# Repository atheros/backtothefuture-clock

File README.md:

Back To The Future Time Circuit Clock
=====================================

About
-----

This repository contains or documents and source code related to my Back To The Future Time Circuit Clock project.

All project details are hosted on hackaday.io: http://hackaday.io/project/709-Back-To-The-Future-Time-Circuit-Clock

This project is part of Hackaday Porjects Sci-Fi contest: http://hackaday.io/page/276

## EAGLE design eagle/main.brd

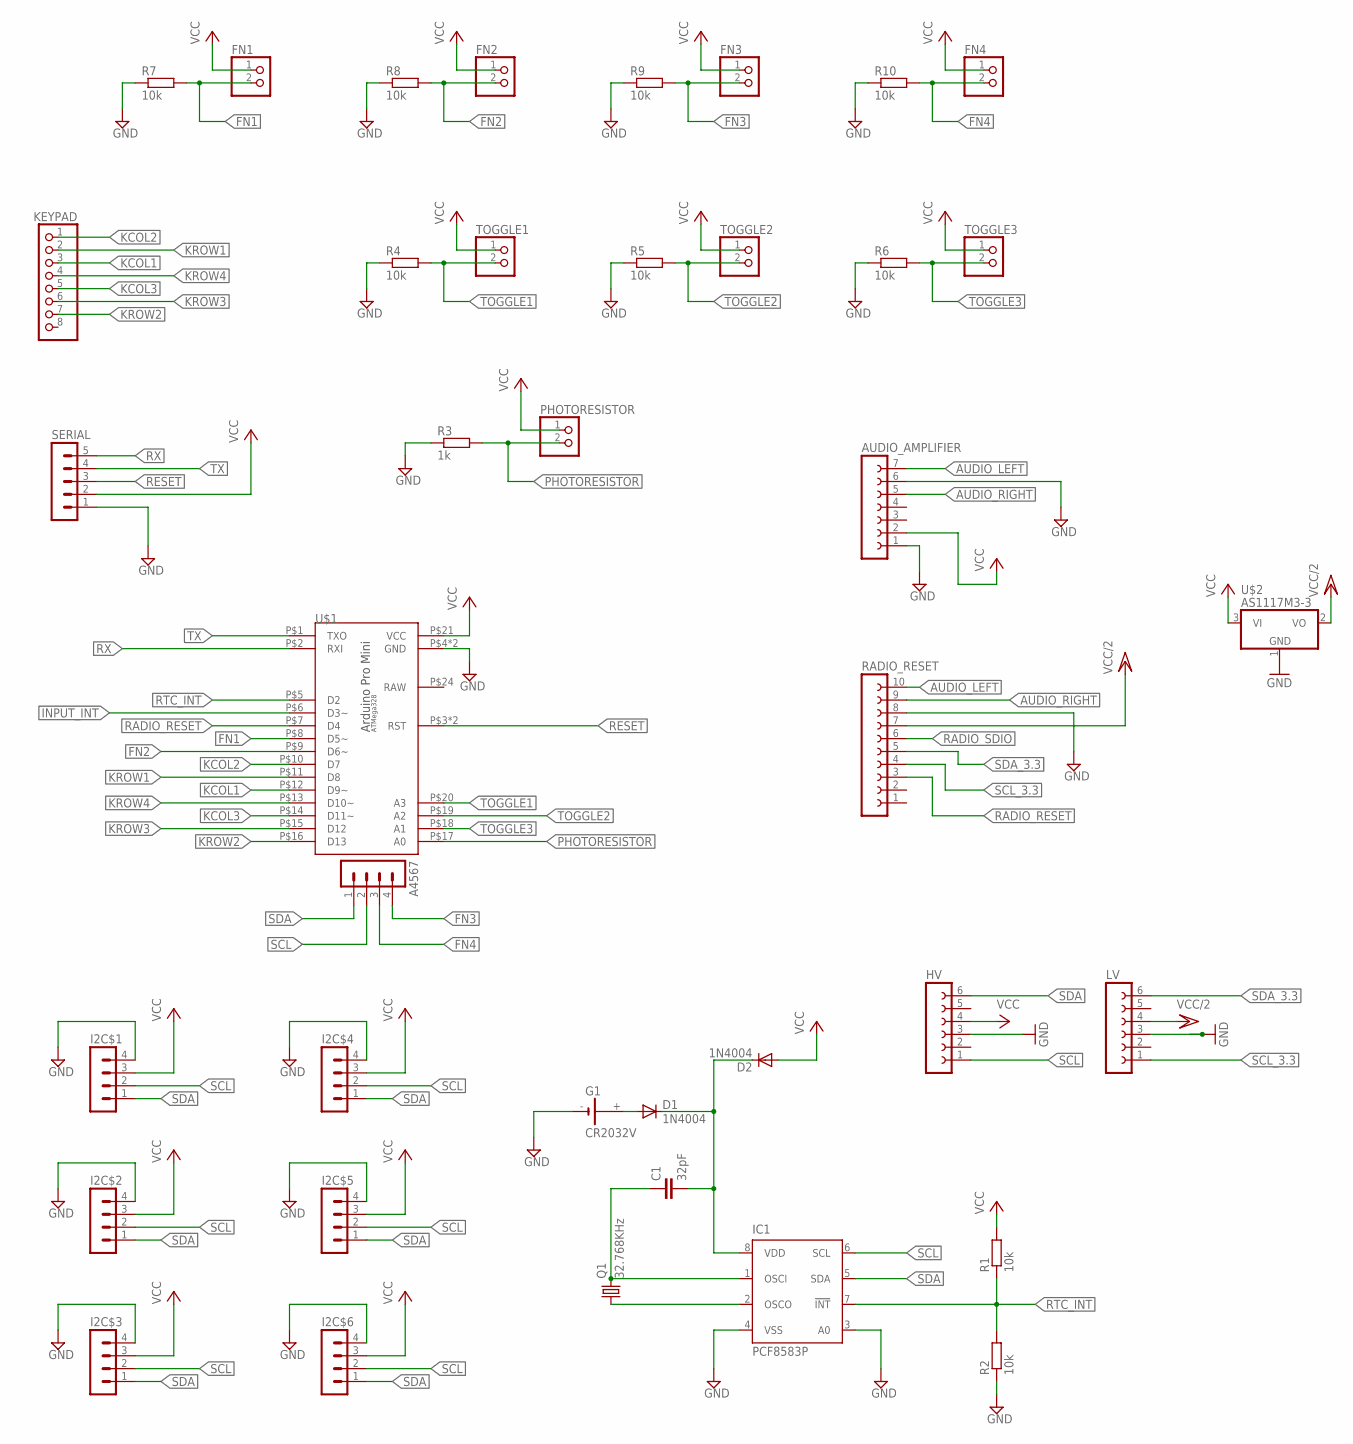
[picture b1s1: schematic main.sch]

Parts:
A4567: MA04-1
AUDIO_AMPLIFIER: FE07-1; FE07
C1: 32pF; C025-024X044
D1, D2: 1N4004; DO41-10
FN1, FN2, FN3, FN4: PINHD-1X2; 1X02
G1: CR2032V
HV: FE06-1; FE06
I2C$1, I2C$2, I2C$3, I2C$4, I2C$5, I2C$6: MA04-1
IC1: PCF8583P; DIL08
KEYPAD: PINHD-1X8; 1X08
LV: FE06-1; FE06
PHOTORESISTOR: PINHD-1X2; 1X02
Q1: 32.768KHz; TC26H
R1, R2, R4, R5, R6, R7, R8, R9, R10: 10k; M0805
R3: 1k; M0805
RADIO_RESET: FE10-1; FE10
SERIAL: MA05-1
TOGGLE1, TOGGLE2, TOGGLE3: PINHD-1X2; 1X02
U$1: ARDUINO-PRO-MINI-BARE; DIP24W
U$2: AS1117M3-3; SOT223

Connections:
AUDIO_LEFT: AUDIO_AMPLIFIER.7, RADIO_RESET.10
AUDIO_RIGHT: AUDIO_AMPLIFIER.5, RADIO_RESET.9
FN1: FN1.2, R7.2, U$1.P$8 (D5~)
FN2: FN2.2, R8.2, U$1.P$9 (D6~)
FN3: A4567.4, FN3.2, R9.2
FN4: A4567.3, FN4.2, R10.2
GND: AUDIO_AMPLIFIER.1, AUDIO_AMPLIFIER.6, G1.-, HV.3, I2C$1.4, I2C$2.4, I2C$3.4, I2C$4.4, I2C$5.4, I2C$6.4, IC1.3 (A0), IC1.4 (VSS), LV.3, R2.1, R3.1, R4.1, R5.1, R6.1, R7.1, R8.1, R9.1, R10.1, RADIO_RESET.8, SERIAL.1, U$1.P$4 (GND), U$1.P$23 (GND), U$2.1 (GND)
INPUT_INT: U$1.P$6 (D3~)
KCOL1: KEYPAD.3, U$1.P$12 (D9~)
KCOL2: KEYPAD.1, U$1.P$10 (D7)
KCOL3: KEYPAD.5, U$1.P$14 (D11~)
KROW1: KEYPAD.2, U$1.P$11 (D8)
KROW2: KEYPAD.7, U$1.P$16 (D13)
KROW3: KEYPAD.6, U$1.P$15 (D12)
KROW4: KEYPAD.4, U$1.P$13 (D10~)
unnamed: C1.1, IC1.1 (OSCI), Q1.2
unnamed: IC1.2 (OSCO), Q1.1
unnamed: D1.A, G1.+
unnamed: C1.2, D1.C, D2.C, IC1.8 (VDD)
PHOTORESISTOR: PHOTORESISTOR.2, R3.2, U$1.P$17 (A0)
RADIO_RESET: RADIO_RESET.3, U$1.P$7 (D4)
RADIO_SDIO: RADIO_RESET.6
RESET: SERIAL.3, U$1.P$3 (RST), U$1.P$22 (RST)
RTC_INT: IC1.7 (!INT), R1.1, R2.2, U$1.P$5 (D2)
RX: SERIAL.5, U$1.P$2 (RXI)
SCL: A4567.2, HV.1, I2C$1.2, I2C$2.2, I2C$3.2, I2C$4.2, I2C$5.2, I2C$6.2, IC1.6 (SCL)
SCL_3.3: LV.1, RADIO_RESET.4
SDA: A4567.1, HV.6, I2C$1.1, I2C$2.1, I2C$3.1, I2C$4.1, I2C$5.1, I2C$6.1, IC1.5 (SDA)
SDA_3.3: LV.6, RADIO_RESET.5
TOGGLE1: R4.2, TOGGLE1.2, U$1.P$20 (A3)
TOGGLE2: R5.2, TOGGLE2.2, U$1.P$19 (A2)
TOGGLE3: R6.2, TOGGLE3.2, U$1.P$18 (A1)
TX: SERIAL.4, U$1.P$1 (TXO)
VCC: AUDIO_AMPLIFIER.2, D2.A, FN1.1, FN2.1, FN3.1, FN4.1, HV.4, I2C$1.3, I2C$2.3, I2C$3.3, I2C$4.3, I2C$5.3, I2C$6.3, PHOTORESISTOR.1, R1.2, SERIAL.2, TOGGLE1.1, TOGGLE2.1, TOGGLE3.1, U$1.P$21 (VCC), U$2.3 (VI)
VCC/2: LV.4, RADIO_RESET.7, U$2.2 (VO)

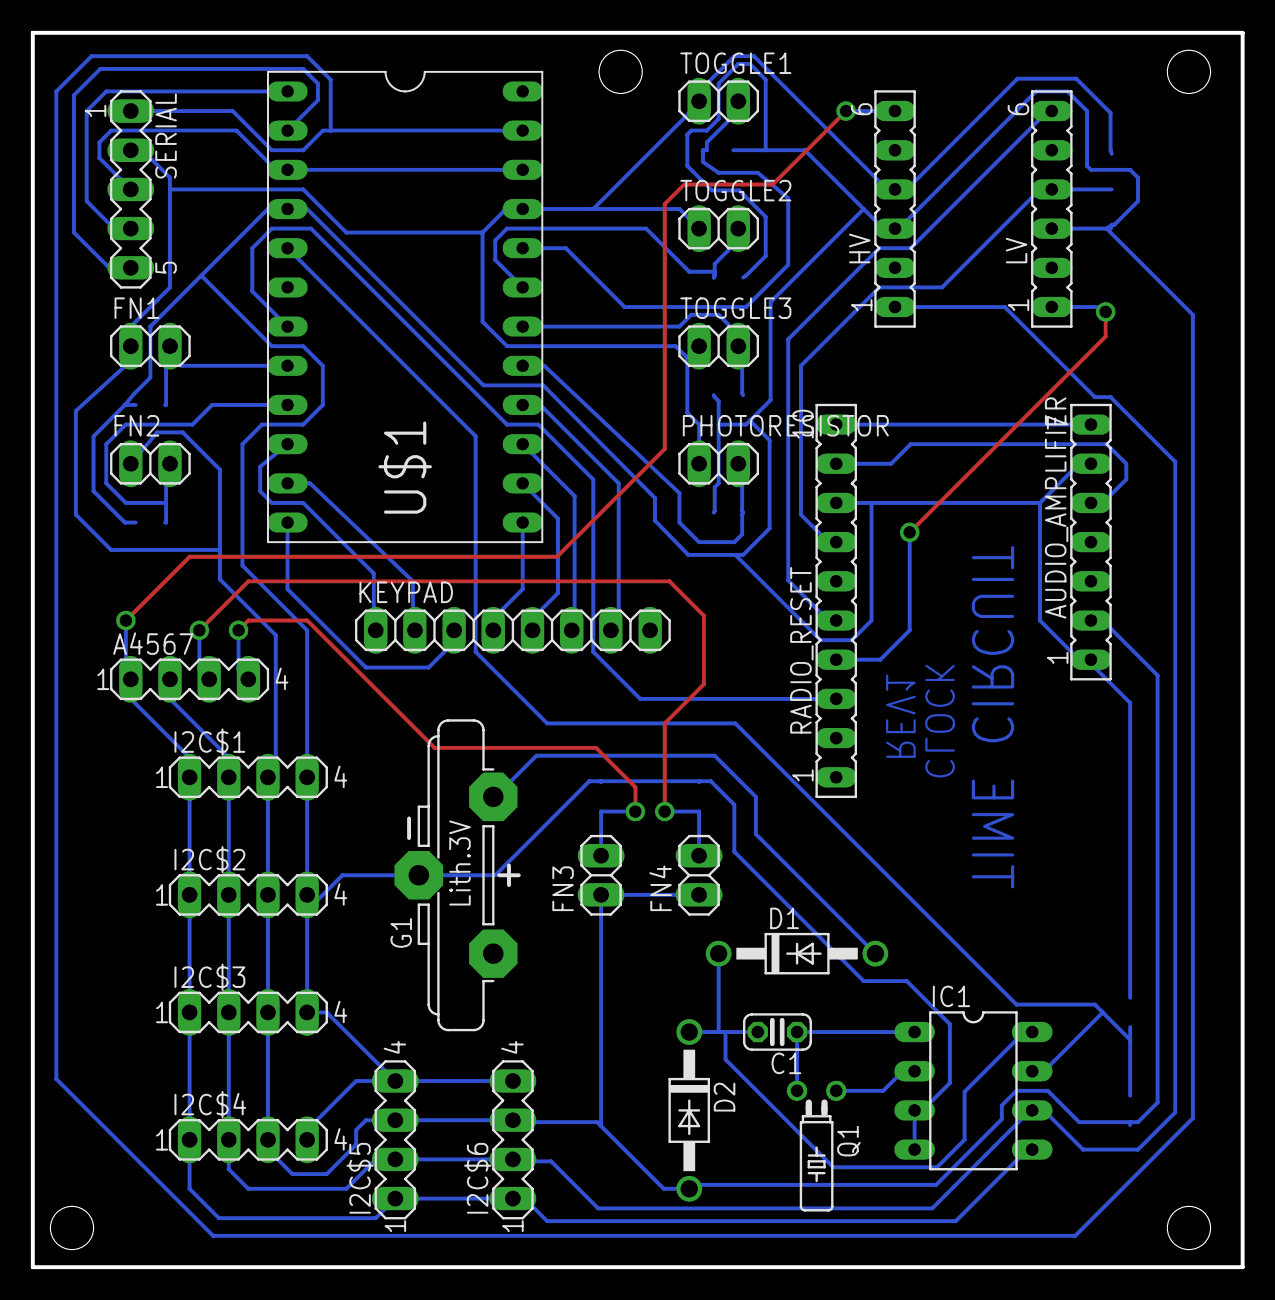
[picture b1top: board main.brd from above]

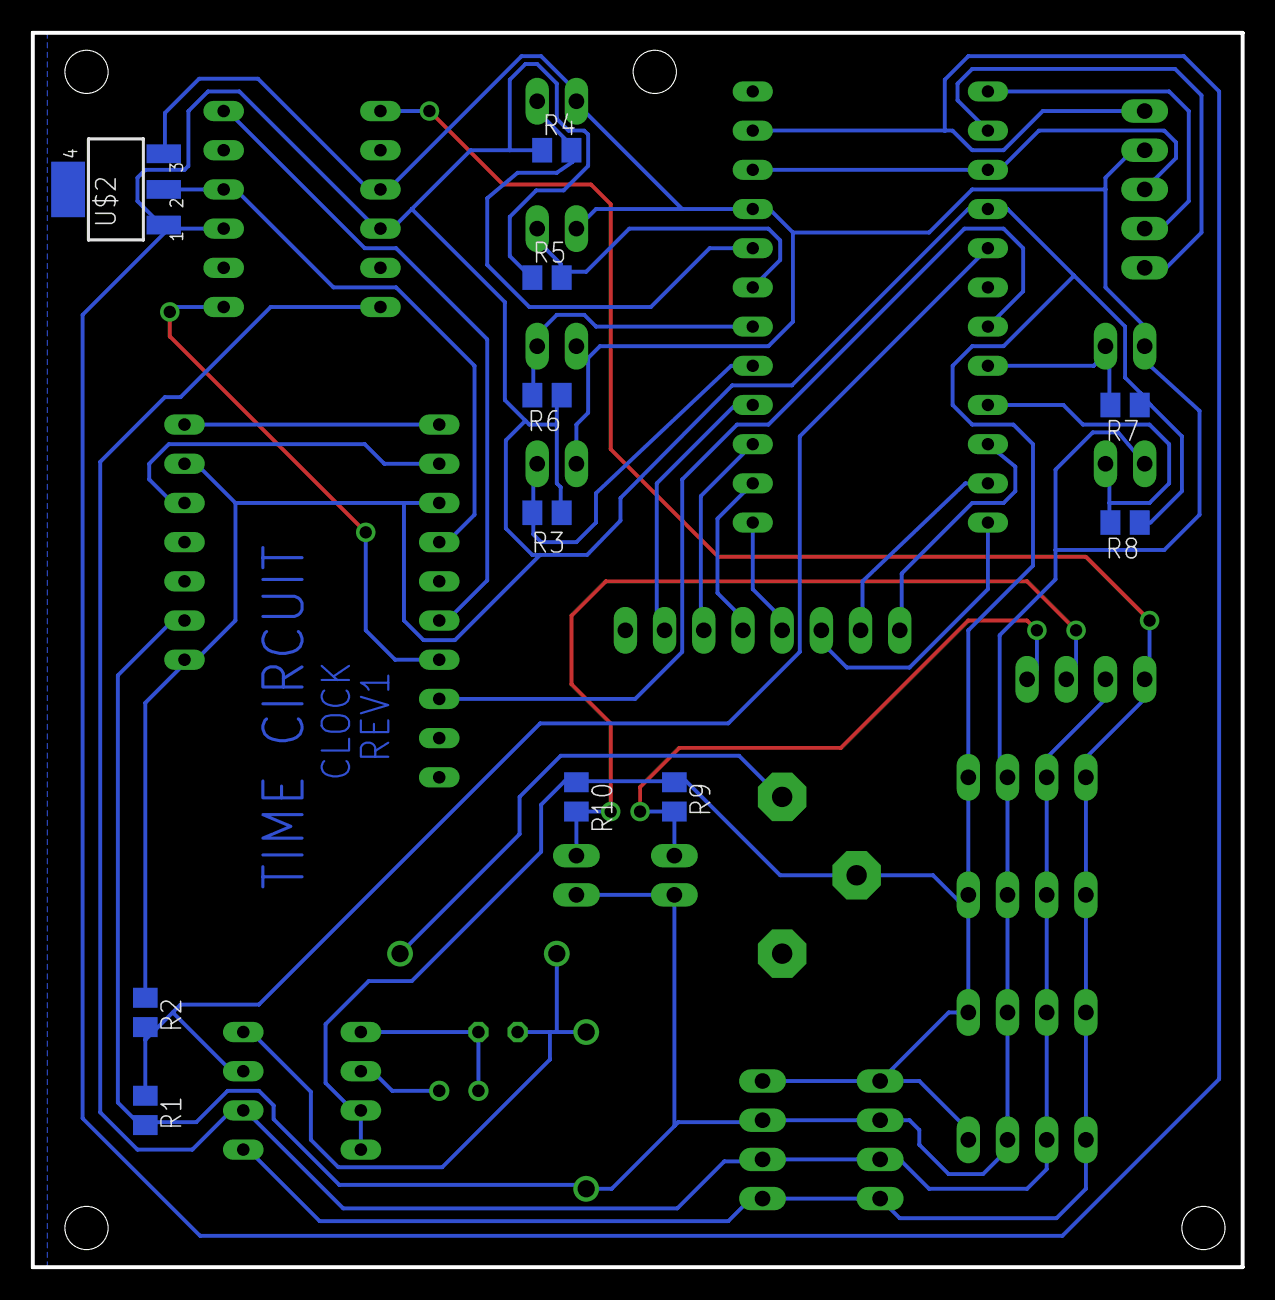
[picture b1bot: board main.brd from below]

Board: 2 copper layers, 78.4 x 80.0 mm, 39 parts (11 on the bottom side), 33 nets.

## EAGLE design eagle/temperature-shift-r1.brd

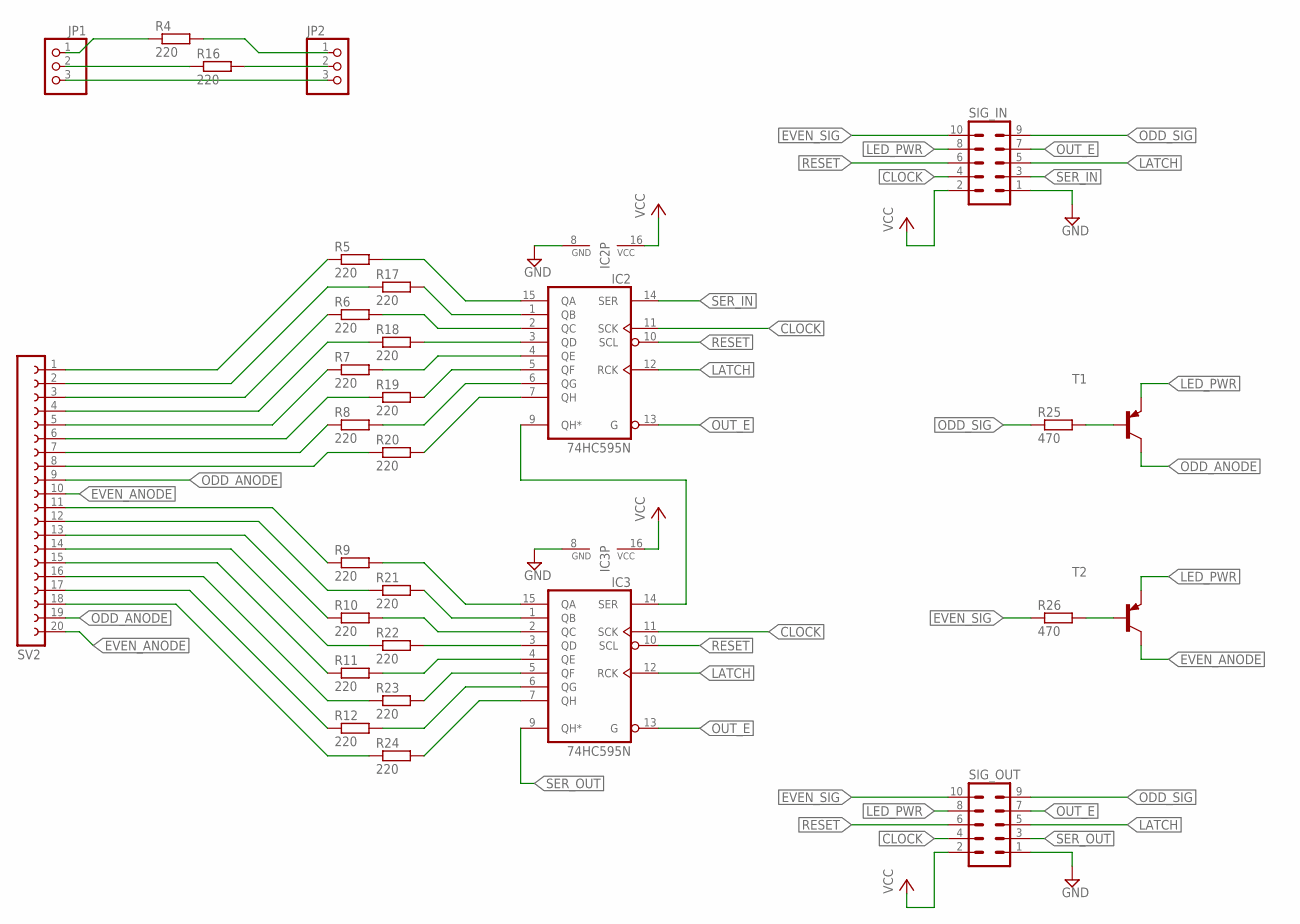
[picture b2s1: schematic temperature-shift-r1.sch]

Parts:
IC2, IC3: 74HC595N; DIL16
JP1, JP2: PINHD-1X3; 1X03
R4, R5, R6, R7, R8, R9, R10, R11, R12, R16, R17, R18, R19, R20, R21, R22, R23, R24: 220; R0805
R25, R26: 470; R0805
SIG_IN: MA05-2
SIG_OUT: MA05-2
SV2: FE20-1; FE20
T1, T2: BC557B-PNP-TO92-EBC; TO92-EBC

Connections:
CLOCK: IC2.11 (SCK), IC3.11 (SCK), SIG_IN.4, SIG_OUT.4
EVEN_ANODE: SV2.10, SV2.20, T2.C
EVEN_SIG: R26.1, SIG_IN.10, SIG_OUT.10
GND: IC2.8 (GND), IC3.8 (GND), SIG_IN.1, SIG_OUT.1
LATCH: IC2.12 (RCK), IC3.12 (RCK), SIG_IN.5, SIG_OUT.5
LED_PWR: SIG_IN.8, SIG_OUT.8, T1.E, T2.E
unnamed: IC2.15 (QA), R5.2
unnamed: IC2.2 (QC), R6.2
unnamed: IC2.4 (QE), R7.2
unnamed: IC2.6 (QG), R8.2
unnamed: R20.1, SV2.8
unnamed: R19.1, SV2.6
unnamed: R18.1, SV2.4
unnamed: R17.1, SV2.2
unnamed: IC2.1 (QB), R17.2
unnamed: IC2.3 (QD), R18.2
unnamed: IC2.5 (QF), R19.2
unnamed: IC2.7 (QH), R20.2
unnamed: IC3.15 (QA), R9.2
unnamed: IC3.2 (QC), R10.2
unnamed: IC3.4 (QE), R11.2
unnamed: IC3.6 (QG), R12.2
unnamed: R24.1, SV2.18
unnamed: R23.1, SV2.16
unnamed: R22.1, SV2.14
unnamed: R21.1, SV2.12
unnamed: IC3.1 (QB), R21.2
unnamed: IC3.3 (QD), R22.2
unnamed: IC3.5 (QF), R23.2
unnamed: IC3.7 (QH), R24.2
unnamed: IC2.9 (QH*), IC3.14 (SER)
unnamed: R5.1, SV2.1
unnamed: R6.1, SV2.3
unnamed: R7.1, SV2.5
unnamed: R8.1, SV2.7
unnamed: R9.1, SV2.11
unnamed: R10.1, SV2.13
unnamed: R11.1, SV2.15
unnamed: R12.1, SV2.17
unnamed: JP1.2, R16.1
unnamed: JP1.1, R4.1
unnamed: JP2.1, R4.2
unnamed: JP1.3, JP2.3
unnamed: JP2.2, R16.2
unnamed: R26.2, T2.B
unnamed: R25.2, T1.B
ODD_ANODE: SV2.9, SV2.19, T1.C
ODD_SIG: R25.1, SIG_IN.9, SIG_OUT.9
OUT_E: IC2.13 (G), IC3.13 (G), SIG_IN.7, SIG_OUT.7
RESET: IC2.10 (SCL), IC3.10 (SCL), SIG_IN.6, SIG_OUT.6
SER_IN: IC2.14 (SER), SIG_IN.3
SER_OUT: IC3.9 (QH*), SIG_OUT.3
VCC: IC2.16 (VCC), IC3.16 (VCC), SIG_IN.2, SIG_OUT.2

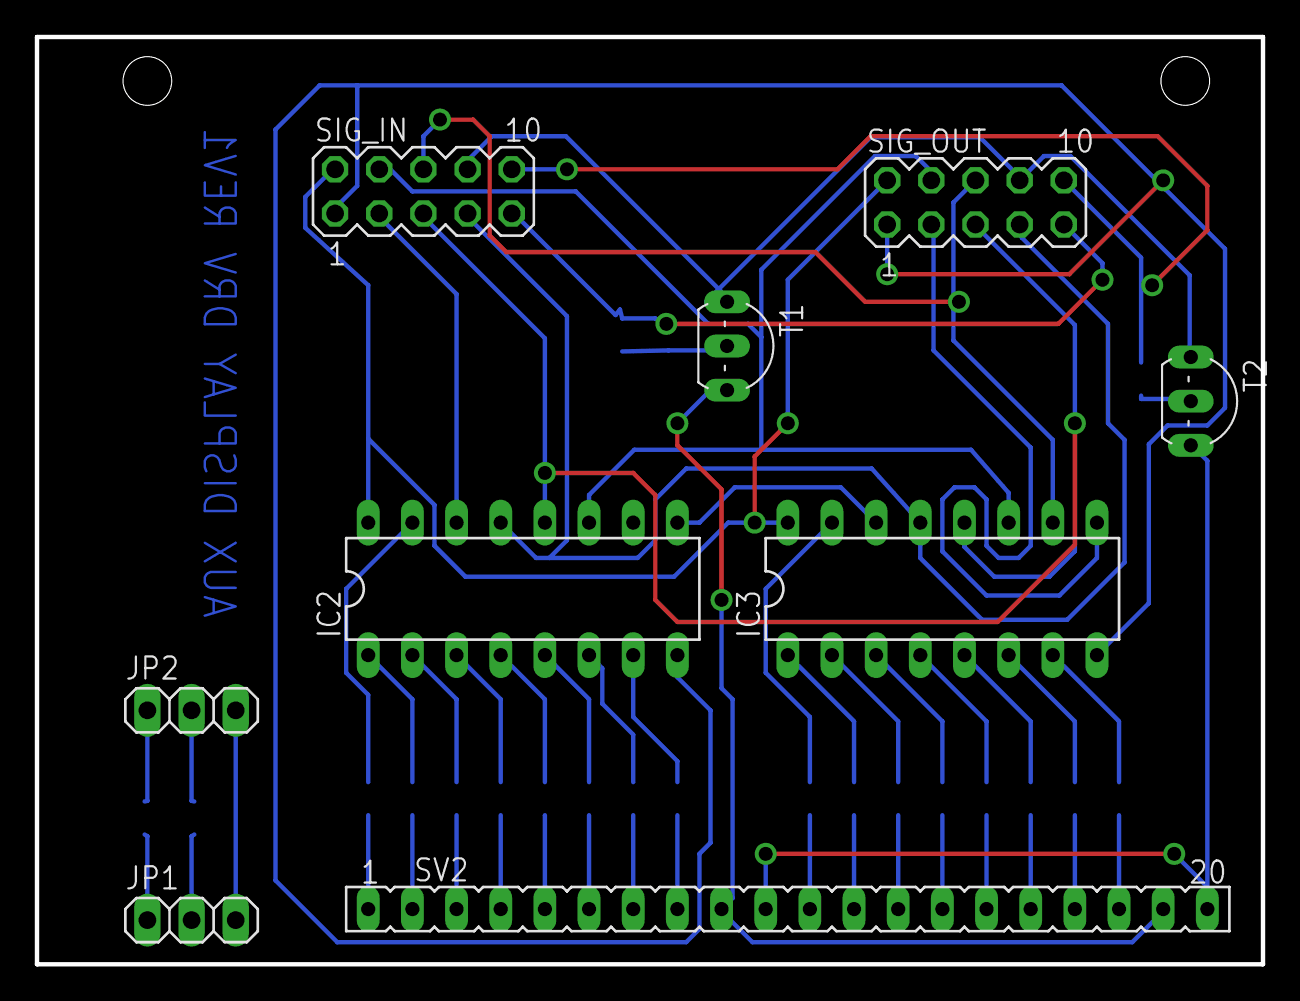
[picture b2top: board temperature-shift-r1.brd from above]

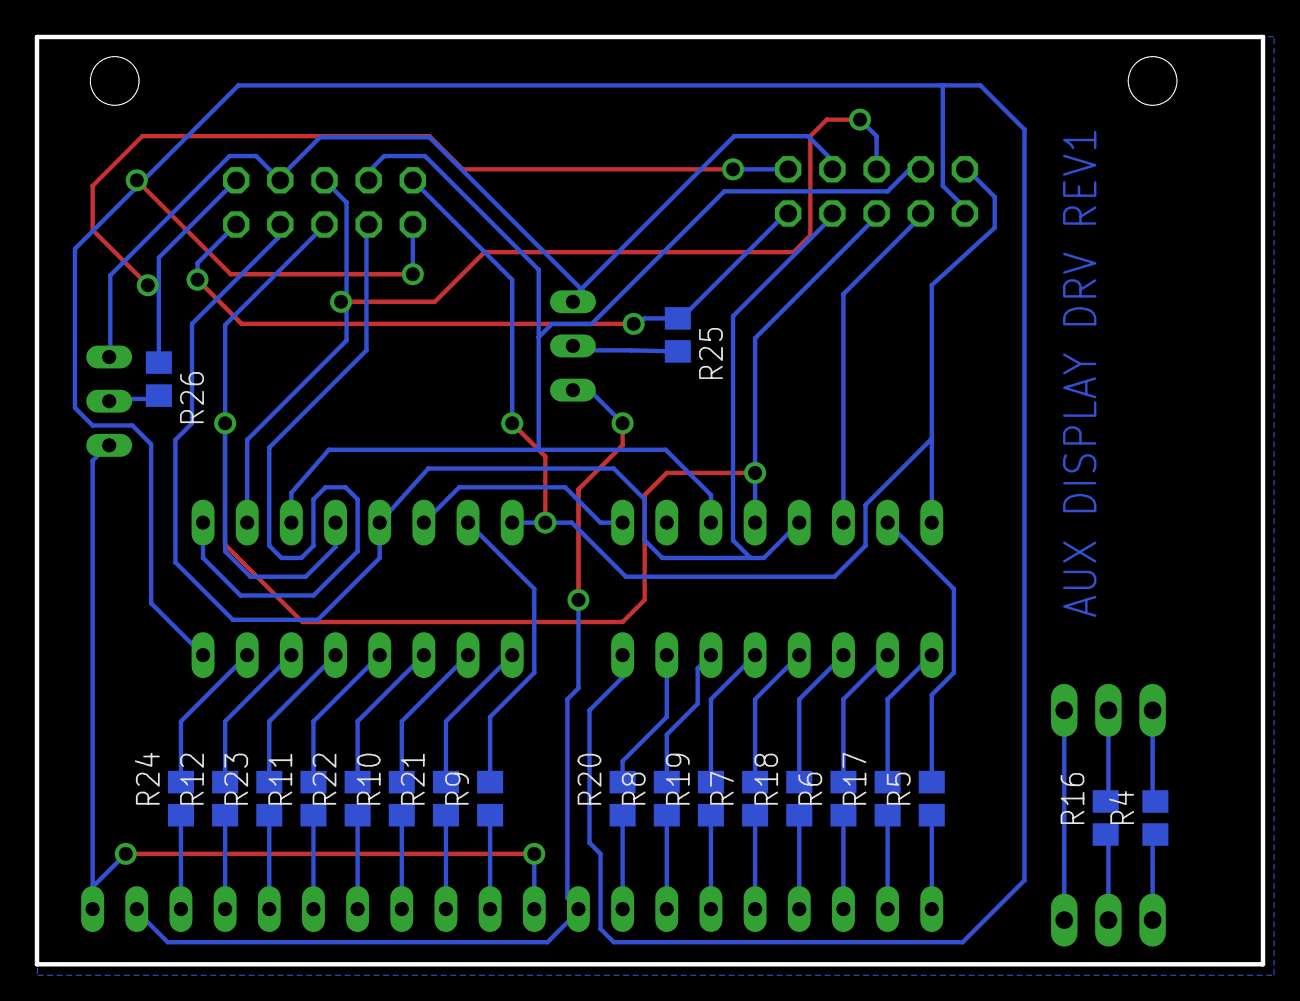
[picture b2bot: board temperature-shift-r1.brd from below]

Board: 2 copper layers, 70.5 x 53.3 mm, 29 parts (20 on the bottom side), 53 nets.

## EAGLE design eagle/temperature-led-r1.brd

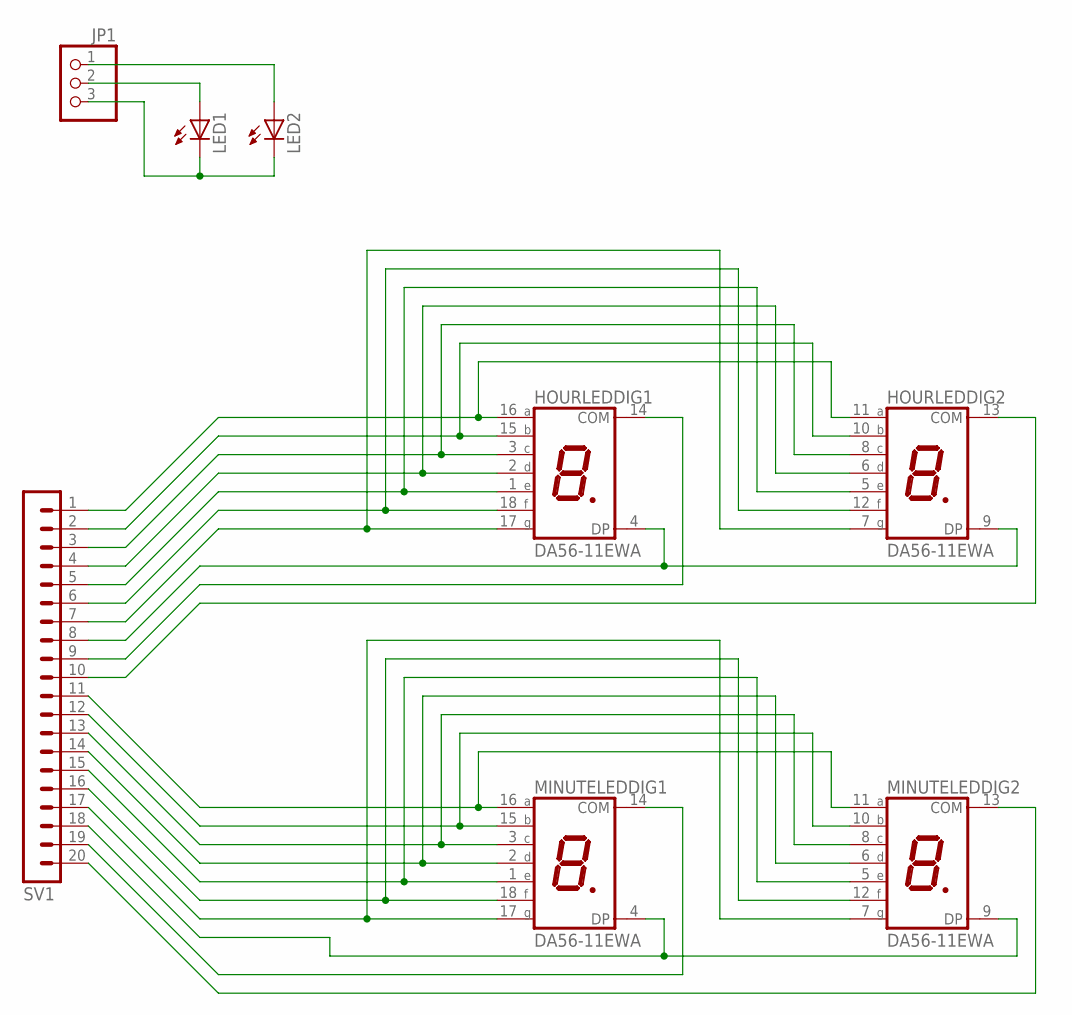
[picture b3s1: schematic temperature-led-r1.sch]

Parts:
HOURLED: DA56-11EWA; DA56
JP1: PINHD-1X3; 1X03
LED1, LED2: LED3MM
MINUTELED: DA56-11EWA; DA56
SV1: MA20-1W

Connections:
unnamed: HOURLED.11 (A), HOURLED.16 (A), SV1.1
unnamed: HOURLED.10 (B), HOURLED.15 (B), SV1.2
unnamed: HOURLED.3 (C), HOURLED.8 (C), SV1.3
unnamed: HOURLED.2 (D), HOURLED.6 (D), SV1.4
unnamed: HOURLED.1 (E), HOURLED.5 (E), SV1.5
unnamed: HOURLED.12 (F), HOURLED.18 (F), SV1.6
unnamed: HOURLED.7 (G), HOURLED.17 (G), SV1.7
unnamed: HOURLED.4 (DP), HOURLED.9 (DP), SV1.8
unnamed: MINUTELED.11 (A), MINUTELED.16 (A), SV1.11
unnamed: MINUTELED.10 (B), MINUTELED.15 (B), SV1.12
unnamed: MINUTELED.3 (C), MINUTELED.8 (C), SV1.13
unnamed: MINUTELED.2 (D), MINUTELED.6 (D), SV1.14
unnamed: MINUTELED.1 (E), MINUTELED.5 (E), SV1.15
unnamed: MINUTELED.12 (F), MINUTELED.18 (F), SV1.16
unnamed: MINUTELED.7 (G), MINUTELED.17 (G), SV1.17
unnamed: MINUTELED.4 (DP), MINUTELED.9 (DP), SV1.18
unnamed: HOURLED.13 (COM), SV1.10
unnamed: JP1.3, LED1.K (C), LED2.K (C)
unnamed: HOURLED.14 (COM), SV1.9
unnamed: JP1.2, LED1.A
unnamed: JP1.1, LED2.A
unnamed: MINUTELED.14 (COM), SV1.19
unnamed: MINUTELED.13 (COM), SV1.20

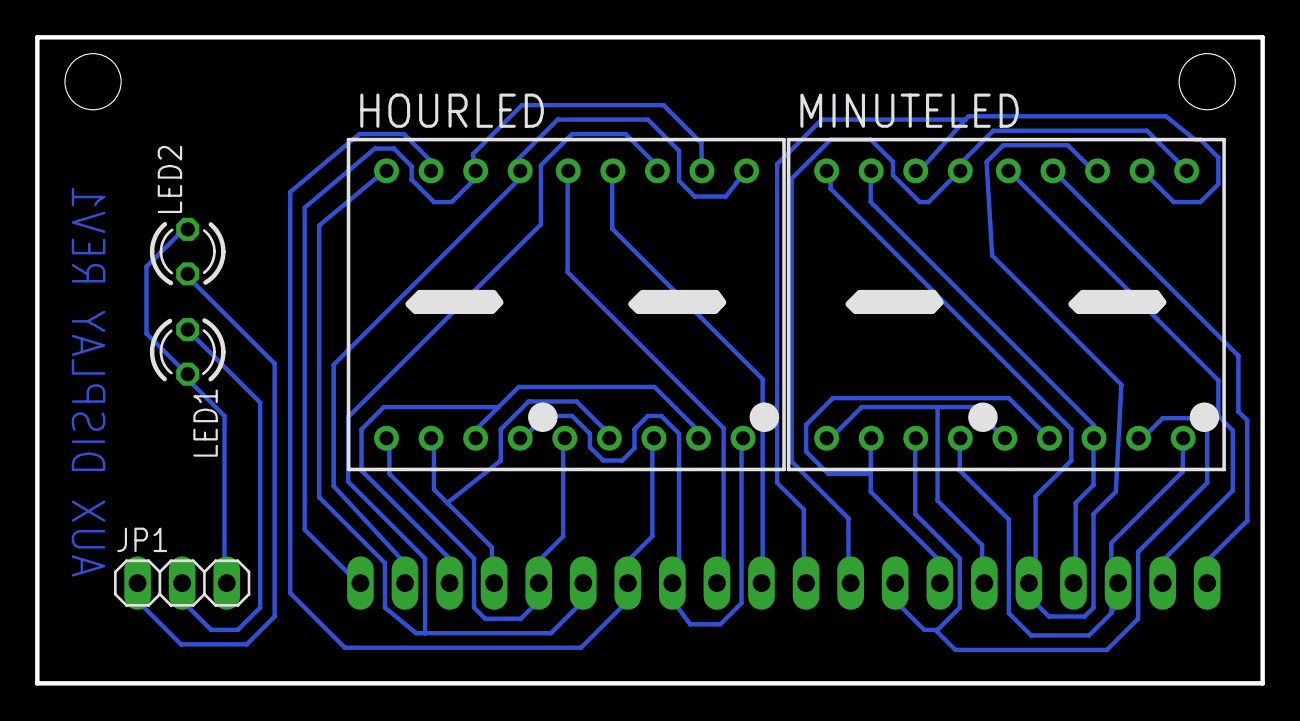
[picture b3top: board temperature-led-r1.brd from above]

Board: 2 copper layers, 69.8 x 36.8 mm, 6 parts (1 on the bottom side), 23 nets.

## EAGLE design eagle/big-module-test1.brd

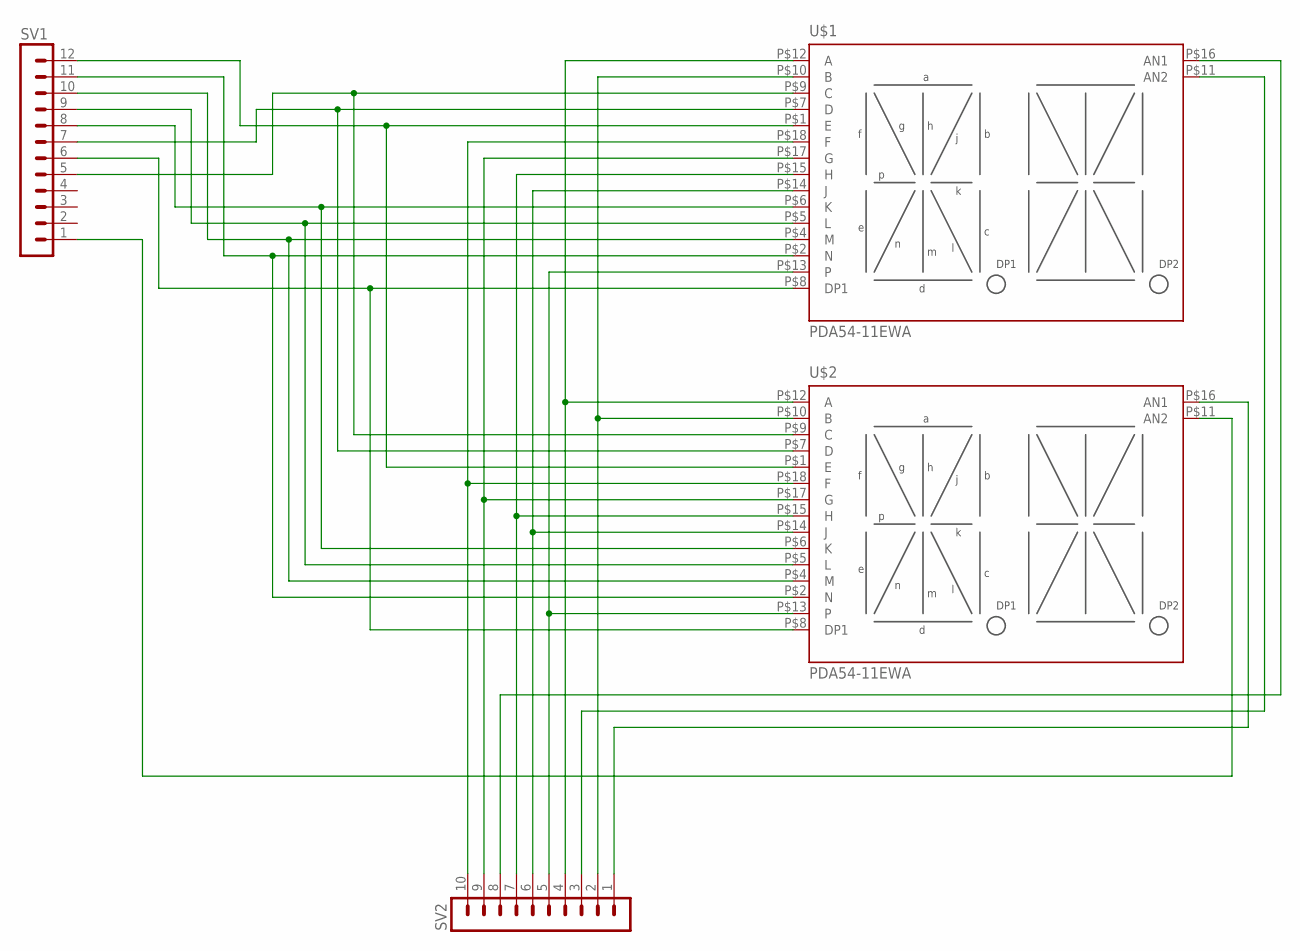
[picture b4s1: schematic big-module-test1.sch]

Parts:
SV1: MA12-1W
SV2: MA10-1
U$1, U$2: PDA54-11EWA; PDA54-11XX

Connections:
unnamed: SV1.12, U$1.P$1 (E), U$2.P$1 (E)
unnamed: SV1.11, U$1.P$2 (N), U$2.P$2 (N)
unnamed: SV1.10, U$1.P$4 (M), U$2.P$4 (M)
unnamed: SV1.9, U$1.P$5 (L), U$2.P$5 (L)
unnamed: SV1.8, U$1.P$6 (K), U$2.P$6 (K)
unnamed: SV1.7, U$1.P$7 (D), U$2.P$7 (D)
unnamed: SV1.6, U$1.P$8 (DP1), U$2.P$8 (DP1)
unnamed: SV1.5, U$1.P$9 (C), U$2.P$9 (C)
unnamed: SV2.10, U$1.P$18 (F), U$2.P$18 (F)
unnamed: SV2.9, U$1.P$17 (G), U$2.P$17 (G)
unnamed: SV2.8, U$1.P$16 (AN1)
unnamed: SV2.7, U$1.P$15 (H), U$2.P$15 (H)
unnamed: SV2.6, U$1.P$14 (J), U$2.P$14 (J)
unnamed: SV2.5, U$1.P$13, U$2.P$13
unnamed: SV2.4, U$1.P$12 (A), U$2.P$12 (A)
unnamed: SV2.3, U$1.P$11 (AN2)
unnamed: SV2.2, U$1.P$10 (B), U$2.P$10 (B)
unnamed: SV2.1, U$2.P$16 (AN1)
unnamed: SV1.1, U$2.P$11 (AN2)

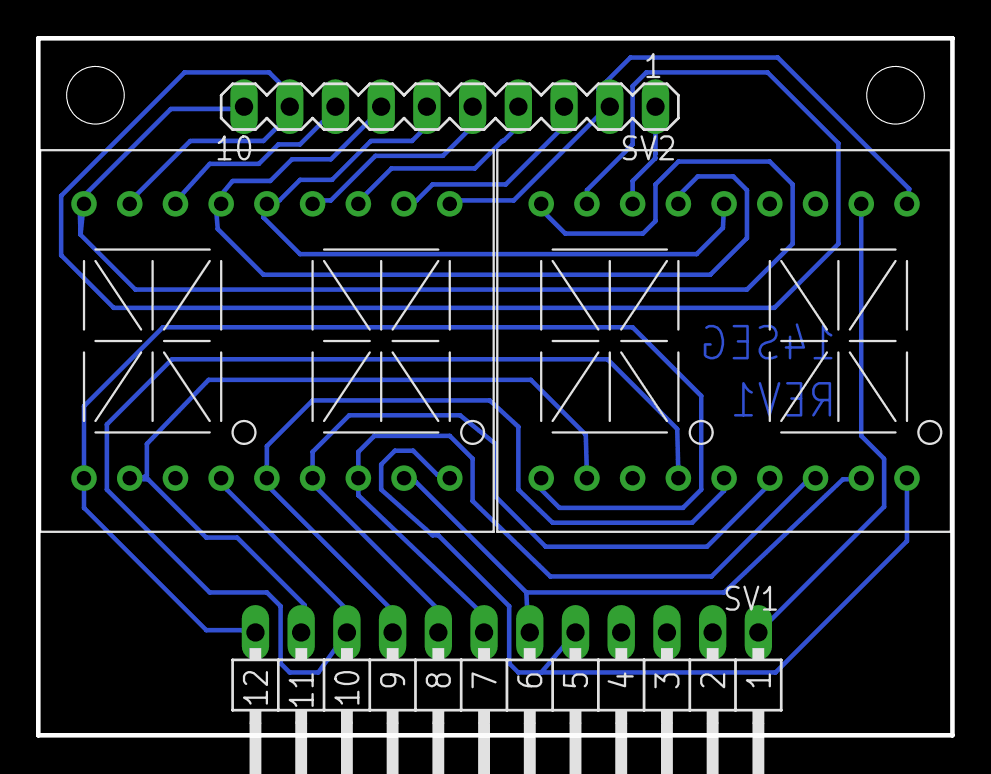
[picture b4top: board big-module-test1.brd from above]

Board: 2 copper layers, 50.8 x 38.7 mm, 4 parts (0 on the bottom side), 19 nets.

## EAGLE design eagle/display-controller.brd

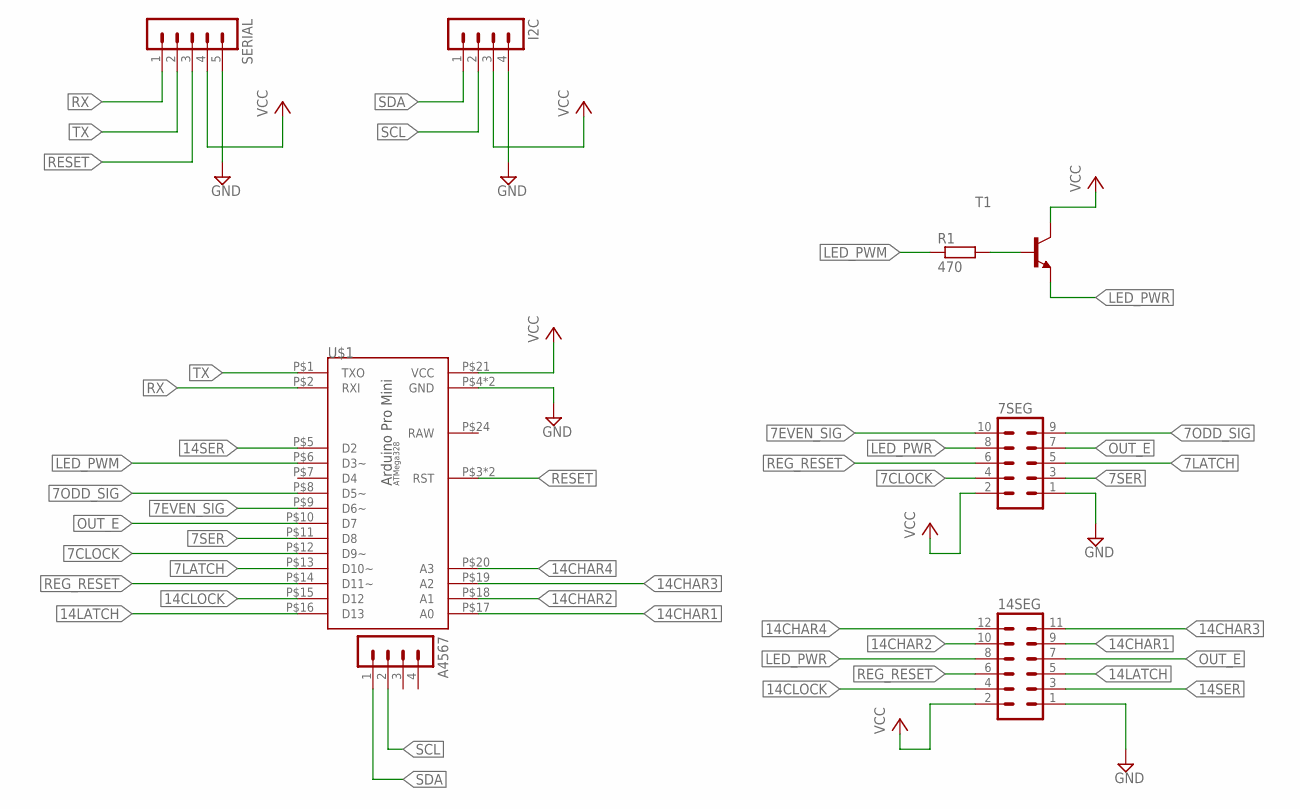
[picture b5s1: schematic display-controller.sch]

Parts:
7SEG: MA05-2
14SEG: MA06-2
A4567: MA04-1
I2C: MA04-1
R1: 470; 0207/2V
SERIAL: MA05-1
T1: BC337-40-NPN-TO92-CBE; TO92-CBE
U$1: ARDUINO-PRO-MINI-BARE; DIP24W

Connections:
7CLOCK: 7SEG.4, U$1.P$12 (D9~)
7EVEN_SIG: 7SEG.10, U$1.P$9 (D6~)
7LATCH: 7SEG.5, U$1.P$13 (D10~)
7ODD_SIG: 7SEG.9, U$1.P$8 (D5~)
7SER: 7SEG.3, U$1.P$11 (D8)
14CHAR1: 14SEG.9, U$1.P$17 (A0)
14CHAR2: 14SEG.10, U$1.P$18 (A1)
14CHAR3: 14SEG.11, U$1.P$19 (A2)
14CHAR4: 14SEG.12, U$1.P$20 (A3)
14CLOCK: 14SEG.4, U$1.P$15 (D12)
14LATCH: 14SEG.5, U$1.P$16 (D13)
14SER: 14SEG.3, U$1.P$5 (D2)
GND: 7SEG.1, 14SEG.1, I2C.4, SERIAL.5, U$1.P$4 (GND), U$1.P$23 (GND)
LED_PWM: R1.1, U$1.P$6 (D3~)
LED_PWR: 7SEG.8, 14SEG.8, T1.E
unnamed: R1.2, T1.B
OUT_E: 7SEG.7, 14SEG.7, U$1.P$10 (D7)
REG_RESET: 7SEG.6, 14SEG.6, U$1.P$14 (D11~)
RESET: SERIAL.3, U$1.P$3 (RST), U$1.P$22 (RST)
RX: SERIAL.1, U$1.P$2 (RXI)
SCL: A4567.2, I2C.2
SDA: A4567.1, I2C.1
TX: SERIAL.2, U$1.P$1 (TXO)
VCC: 7SEG.2, 14SEG.2, I2C.3, SERIAL.4, T1.C, U$1.P$21 (VCC)

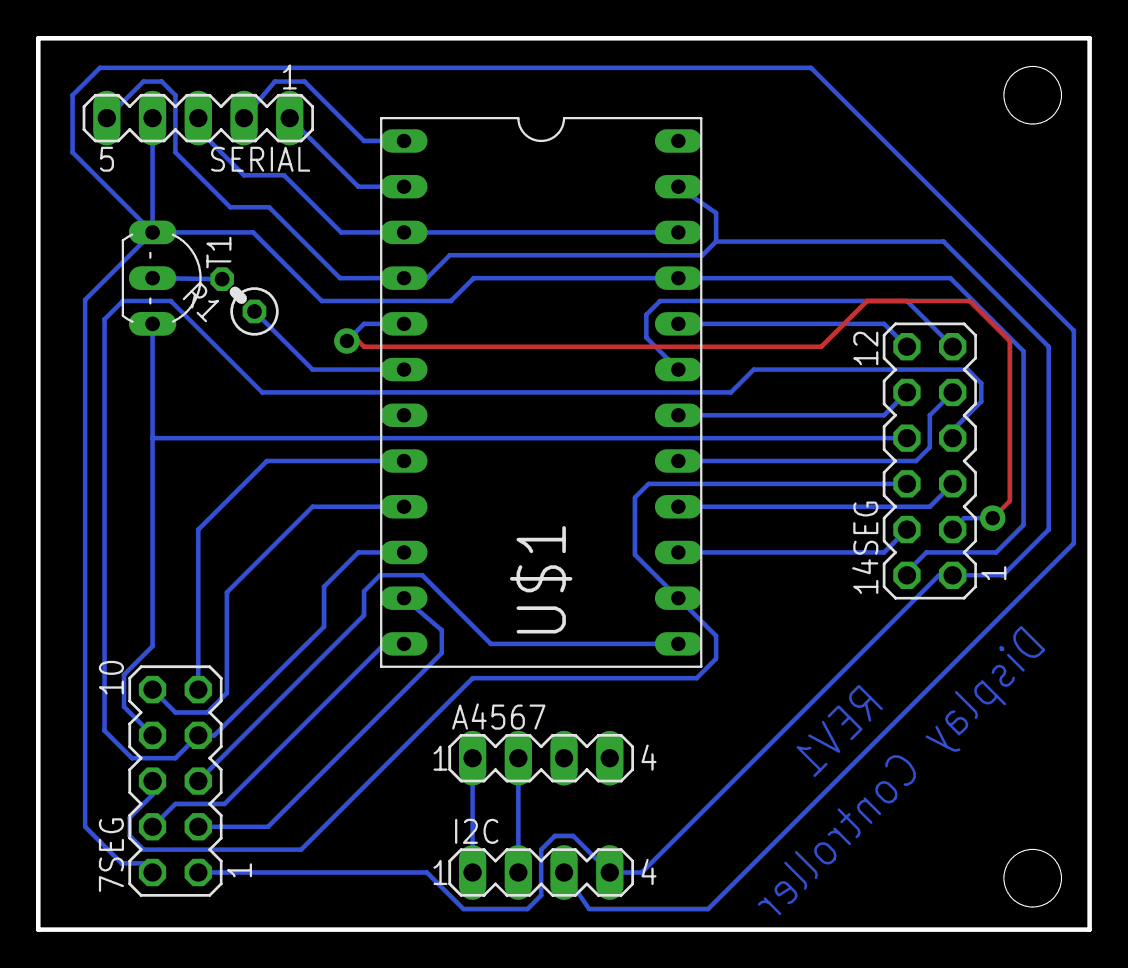
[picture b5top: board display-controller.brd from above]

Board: 2 copper layers, 58.4 x 49.5 mm, 8 parts (0 on the bottom side), 24 nets.

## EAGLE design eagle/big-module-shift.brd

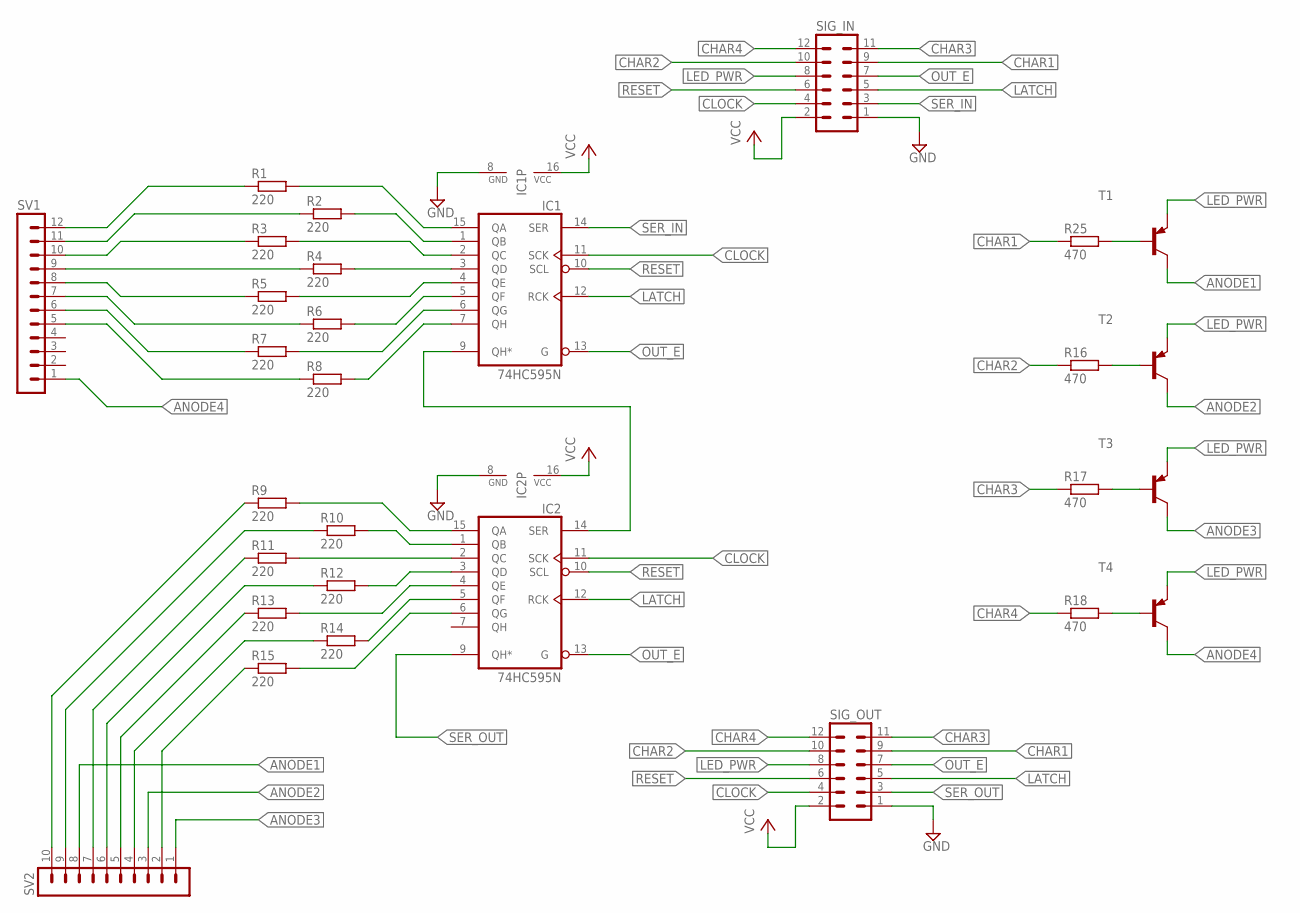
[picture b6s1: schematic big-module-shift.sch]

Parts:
IC1, IC2: 74HC595N; DIL16
R1, R2, R3, R4, R5, R6, R7, R8, R9, R10, R11, R12, R13, R14, R15: 220; M0805
R16, R17, R18, R25: 470; R0805
SIG_IN: MA06-2
SIG_OUT: MA06-2
SV1: MA12-1
SV2: MA10-1
T1, T2, T3, T4: BC557B-PNP-TO92-EBC; TO92-EBC

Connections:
ANODE1: SV2.8, T1.C
ANODE2: SV2.3, T2.C
ANODE3: SV2.1, T3.C
ANODE4: SV1.1, T4.C
CHAR1: R25.1, SIG_IN.9, SIG_OUT.9
CHAR2: R16.1, SIG_IN.10, SIG_OUT.10
CHAR3: R17.1, SIG_IN.11, SIG_OUT.11
CHAR4: R18.1, SIG_IN.12, SIG_OUT.12
CLOCK: IC1.11 (SCK), IC2.11 (SCK), SIG_IN.4, SIG_OUT.4
GND: IC1.8 (GND), IC2.8 (GND), SIG_IN.1, SIG_OUT.1
LATCH: IC1.12 (RCK), IC2.12 (RCK), SIG_IN.5, SIG_OUT.5
LED_PWR: SIG_IN.8, SIG_OUT.8, T1.E, T2.E, T3.E, T4.E
unnamed: IC1.15 (QA), R1.2
unnamed: IC1.1 (QB), R2.2
unnamed: IC1.2 (QC), R3.2
unnamed: IC1.3 (QD), R4.2
unnamed: IC1.4 (QE), R5.2
unnamed: IC1.5 (QF), R6.2
unnamed: IC1.6 (QG), R7.2
unnamed: IC1.7 (QH), R8.2
unnamed: R1.1, SV1.12
unnamed: R2.1, SV1.11
unnamed: R3.1, SV1.10
unnamed: R4.1, SV1.9
unnamed: R5.1, SV1.8
unnamed: R6.1, SV1.7
unnamed: R7.1, SV1.6
unnamed: R8.1, SV1.5
unnamed: IC1.9 (QH*), IC2.14 (SER)
unnamed: IC2.15 (QA), R9.2
unnamed: IC2.1 (QB), R10.2
unnamed: IC2.2 (QC), R11.2
unnamed: IC2.3 (QD), R12.2
unnamed: IC2.4 (QE), R13.2
unnamed: IC2.5 (QF), R14.2
unnamed: IC2.6 (QG), R15.2
unnamed: R9.1, SV2.10
unnamed: R10.1, SV2.9
unnamed: R11.1, SV2.7
unnamed: R12.1, SV2.6
unnamed: R13.1, SV2.5
unnamed: R14.1, SV2.4
unnamed: R15.1, SV2.2
unnamed: R16.2, T2.B
unnamed: R17.2, T3.B
unnamed: R18.2, T4.B
unnamed: R25.2, T1.B
OUT_E: IC1.13 (G), IC2.13 (G), SIG_IN.7, SIG_OUT.7
RESET: IC1.10 (SCL), IC2.10 (SCL), SIG_IN.6, SIG_OUT.6
SER_IN: IC1.14 (SER), SIG_IN.3
SER_OUT: IC2.9 (QH*), SIG_OUT.3
VCC: IC1.16 (VCC), IC2.16 (VCC), SIG_IN.2, SIG_OUT.2

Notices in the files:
parts and their libraries:
eagle-library-edeca.net-v5-mix: This is v1 and is licensed under the Creative Commons (Attribution-Non-Commercial-Share Alike 2.0 UK)
